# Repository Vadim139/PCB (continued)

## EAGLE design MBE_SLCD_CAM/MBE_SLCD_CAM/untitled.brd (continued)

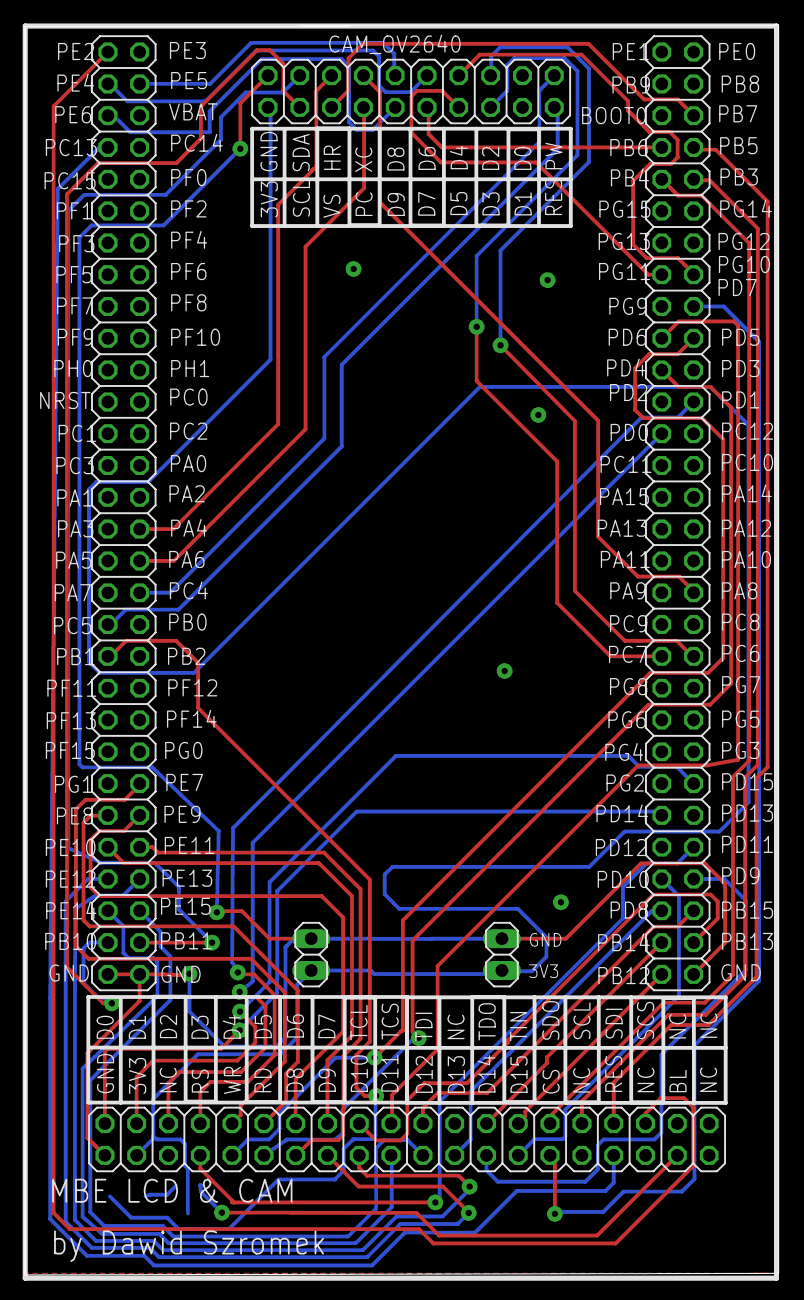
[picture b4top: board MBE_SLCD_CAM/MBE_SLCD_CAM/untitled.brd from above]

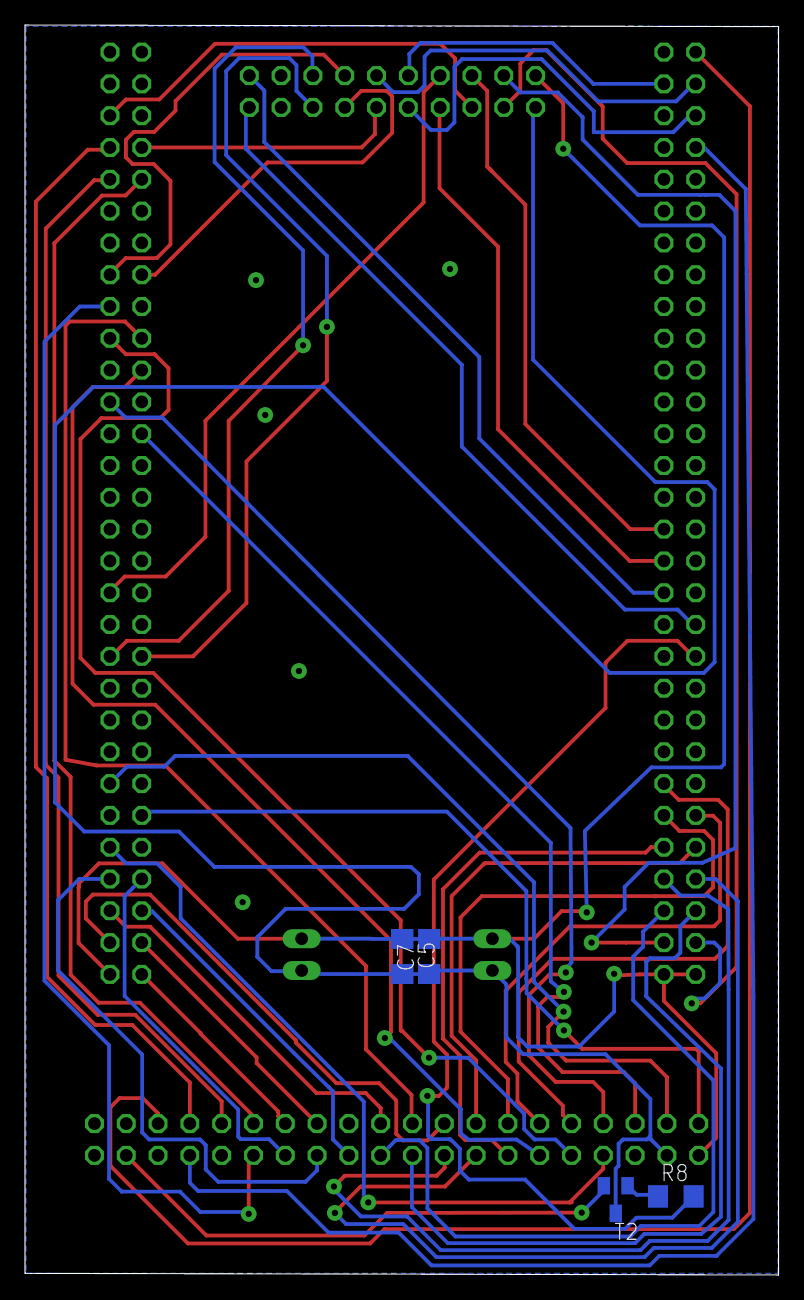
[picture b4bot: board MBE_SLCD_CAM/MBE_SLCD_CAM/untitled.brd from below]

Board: 2 copper layers, 60.2 x 99.8 mm, 7 parts (4 on the bottom side), 51 nets.

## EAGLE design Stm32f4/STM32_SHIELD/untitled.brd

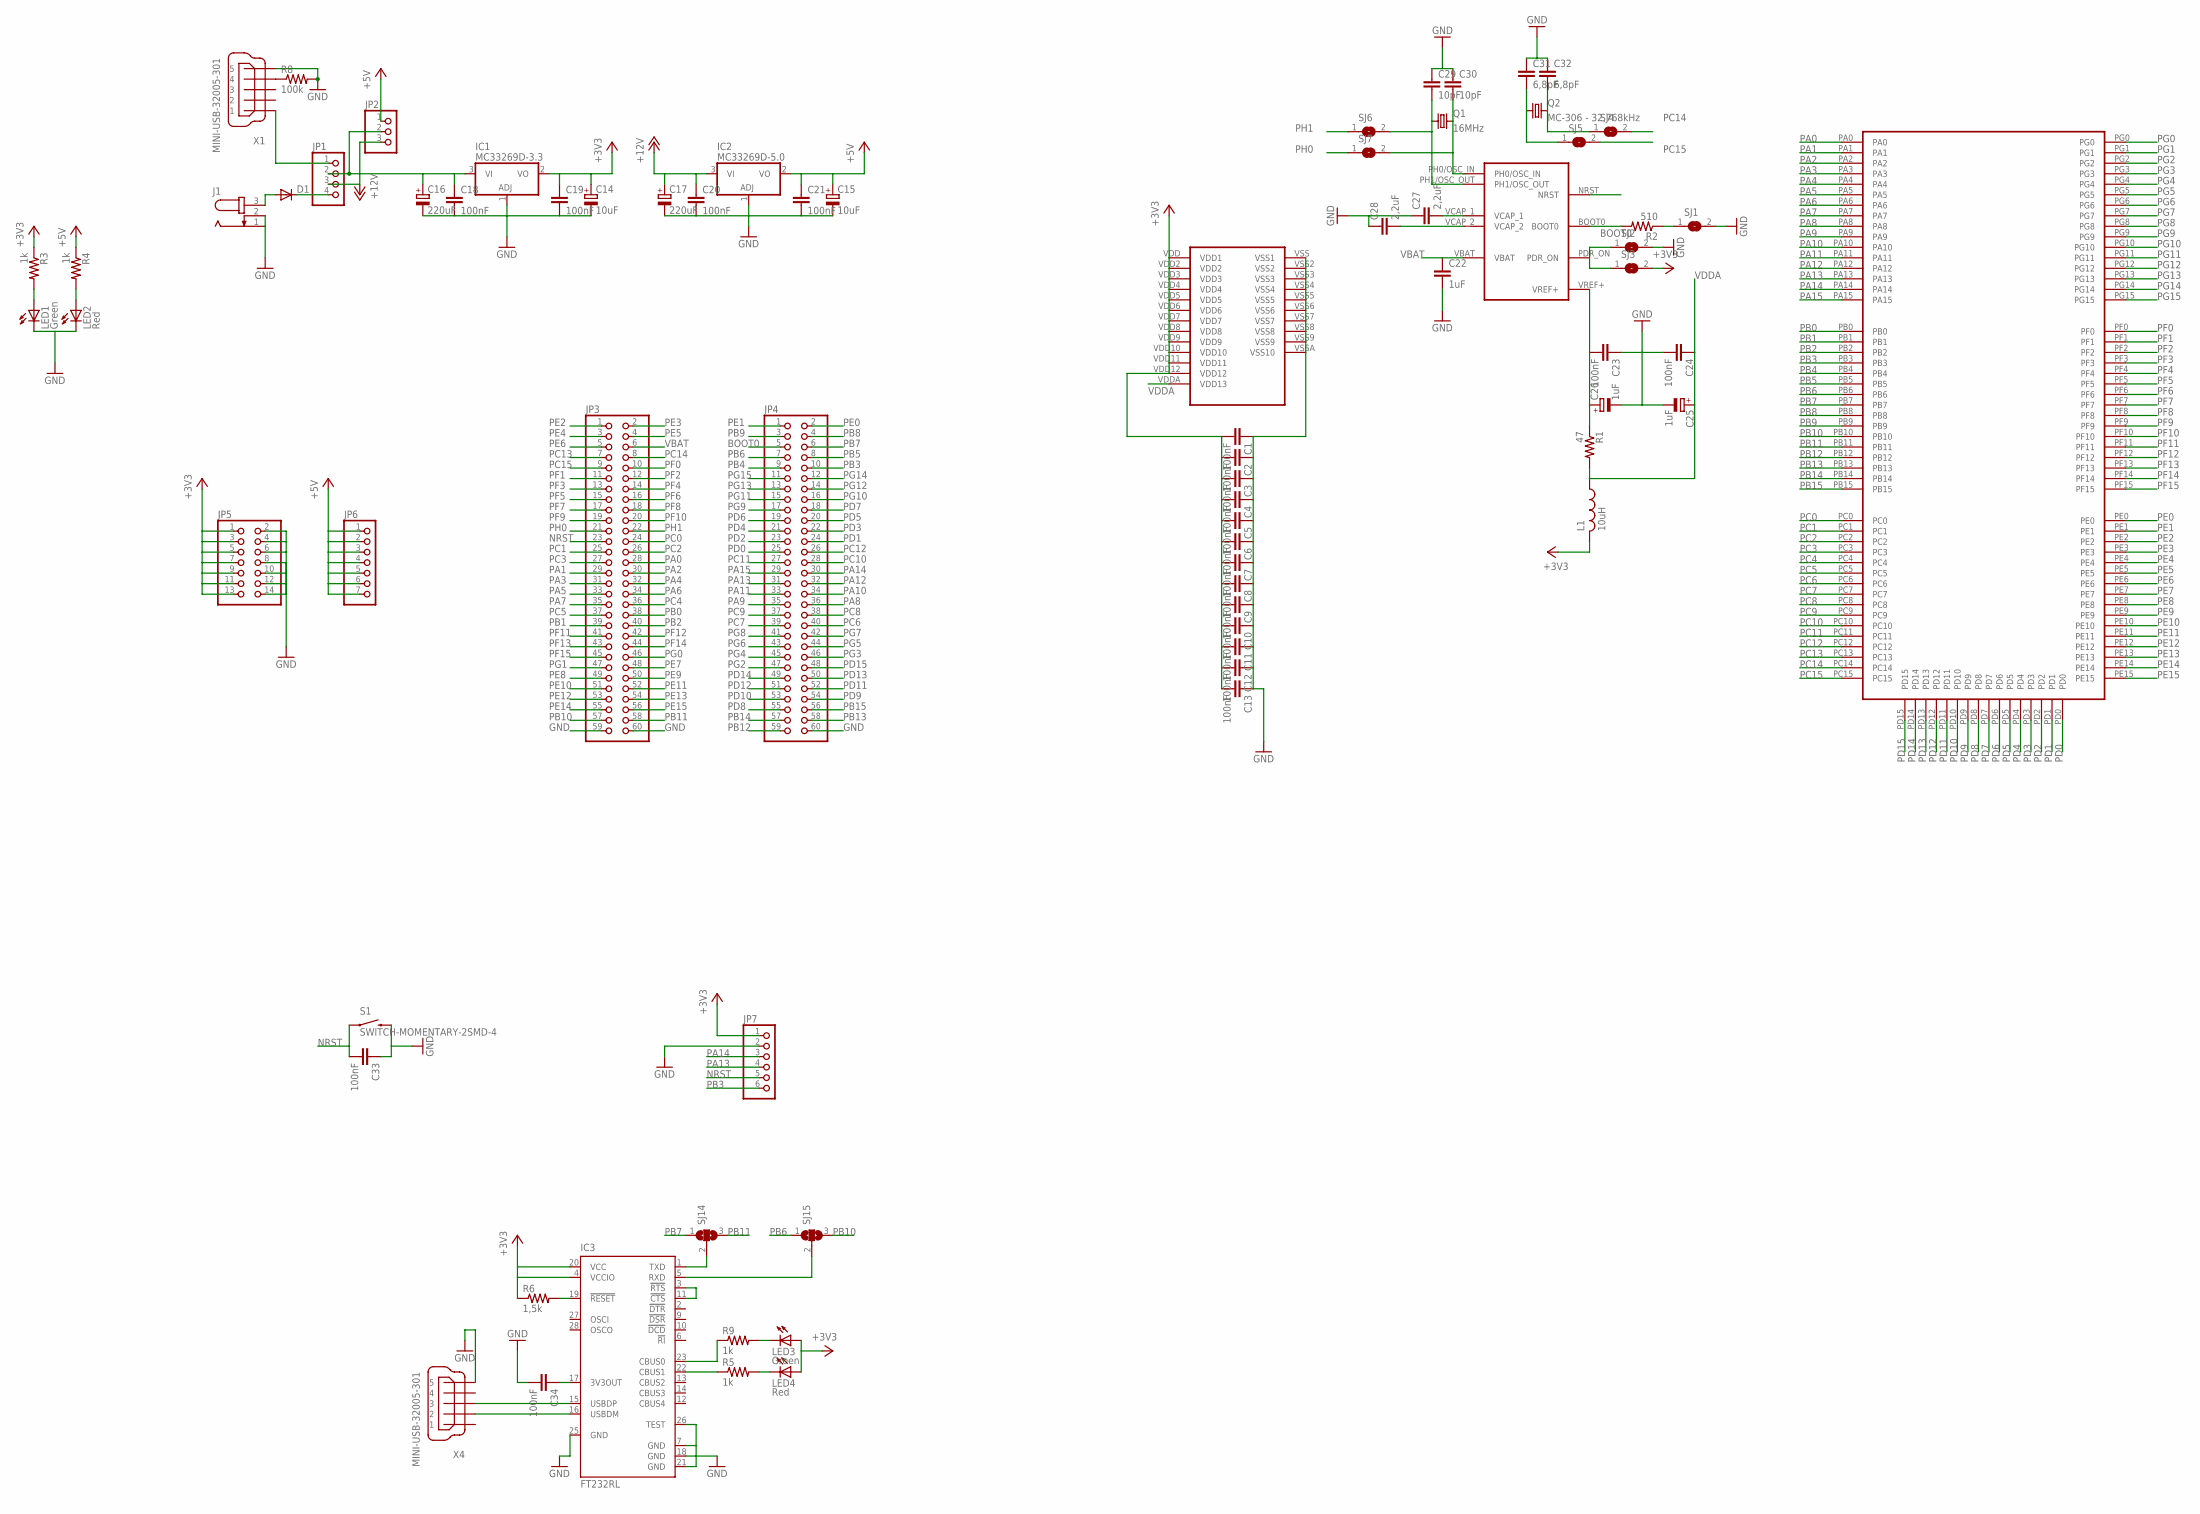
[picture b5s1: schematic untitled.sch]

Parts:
C1, C2, C3, C4, C5, C6, C7, C8, C9, C10, C11, C12, C13, C18, C19, C20, C21, C23, C24, C33, C34: 100nF; C2012
C14, C15: 10uF; SMC_C
C16, C17: 220uF; PANASONIC_D
C22: 1uF; C2012
C25, C26: 1uF; SMC_A
C27, C28: 2,2uF; C2012
C29, C30: 10pF; C2012
C31, C32: 6,8pF; C2012
D1: DIODE-SOD323-W; SOD323-W
IC1: MC33269D-3.3; DPACK
IC2: MC33269D-5.0; DPACK
IC3: FT232RL; SSOP28
J1: JACK-PLUG1; SPC4078
JP1: PINHD-1X4; 1X04
JP2: PINHD-1X3; 1X03
JP3, JP4: PINHD-2X30; 2X30
JP5: PINHD-2X7; 2X07
JP6: PINHD-1X7; 1X07
JP7: PINHD-1X6; 1X06
L1: 10uH; L2012C
LED1, LED3: Green; CHIP-LED0805
LED2, LED4: Red; CHIP-LED0805
Q1: 16MHz; HC49UP
Q2: MC-306 - 32,768kHz; MC-306
R1: 47; R0805
R2: 510; R0805
R3, R4, R5, R9: 1k; R0805
R6: 1,5k; R0805
R8: 100k; R0805
S1: SWITCH-MOMENTARY-2SMD-4; TACTILE_SWITCH_TALL
SJ1, SJ2, SJ3, SJ4, SJ5, SJ6, SJ7: SJ
SJ14, SJ15: SJ2W; SJ_2
U$1: STM32F407LQFP144; LQFP144_20
X1, X4: MINI-USB-32005-301; 32005-301

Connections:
+3V3: C1.2, C2.2, C3.2, C4.2, C5.2, C6.2, C7.2, C8.2, C9.2, C10.2, C11.2, C12.2, C13.2, C14.+, C19.1, IC1.2 (VO), IC3.4 (VCCIO), IC3.20 (VCC), JP5.1, JP5.3, JP5.5, JP5.7, JP5.9, JP5.11, JP5.13, JP7.1, L1.2, LED3.A, LED4.A, R3.1, R6.1, SJ3.2, U$1.VDD (VDD1), U$1.VDD2, U$1.VDD3, U$1.VDD4, U$1.VDD5, U$1.VDD6, U$1.VDD7, U$1.VDD8, U$1.VDD9, U$1.VDD10, U$1.VDD11, U$1.VDD12
+5V: C15.+, C21.1, IC2.2 (VO), JP2.1, JP6.1, JP6.2, JP6.3, JP6.4, JP6.5, JP6.6, JP6.7, R4.1
+12V: C17.+, C20.1, IC2.3 (VI), JP1.3, JP2.3
BOOT0: JP4.5, R2.2, U$1.BOOT0
GND: C1.1, C2.1, C3.1, C4.1, C5.1, C6.1, C7.1, C8.1, C9.1, C10.1, C11.1, C12.1, C13.1, C14.-, C15.-, C16.-, C17.-, C18.2, C19.2, C20.2, C21.2, C22.2, C23.1, C24.2, C25.-, C26.-, C27.1, C28.1, C29.1, C30.1, C31.1, C32.1, C33.1, C34.2, IC1.1 (ADJ), IC2.1 (ADJ), IC3.7 (GND), IC3.18 (GND), IC3.21 (GND), IC3.25 (GND), IC3.26 (TEST), J1.1, J1.2, JP3.59, JP3.60, JP4.60, JP5.2, JP5.4, JP5.6, JP5.8, JP5.10, JP5.12, JP5.14, JP7.2, LED1.C, LED2.C, R8.2, S1.B2 (2), SJ1.2, SJ2.2, U$1.VSS (VSS1), U$1.VSS2, U$1.VSS3, U$1.VSS4, U$1.VSS5, U$1.VSS6, U$1.VSS7, U$1.VSS8, U$1.VSS9, U$1.VSSA (VSS10), X1.5, X4.5
unnamed: JP1.1, X1.1
unnamed: D1.A, J1.3
unnamed: D1.C, JP1.4
unnamed: LED1.A, R3.2
unnamed: R2.1, SJ1.1
unnamed: LED2.A, R4.2
unnamed: C16.+, C18.1, IC1.3 (VI), JP1.2, JP2.2
unnamed: C34.1, IC3.17 (3V3OUT)
unnamed: IC3.19 (!RESET), R6.2
unnamed: IC3.23 (CBUS0), R9.1
unnamed: IC3.16 (USBDM), X4.2
unnamed: IC3.15 (USBDP), X4.3
unnamed: R8.1, X1.4
unnamed: IC3.1 (TXD), SJ14.2
unnamed: IC3.5 (RXD), SJ15.2
unnamed: SJ2.1, SJ3.1, U$1.PDR_ON
unnamed: LED3.C, R9.2
unnamed: LED4.C, R5.2
unnamed: C31.2, Q2.1, SJ5.1
unnamed: C32.2, Q2.4 (2), SJ4.1
unnamed: IC3.22 (CBUS1), R5.1
unnamed: IC3.3 (!RTS), IC3.11 (!CTS)
NRST: C33.2, JP3.23, JP7.5, S1.A2 (1), U$1.NRST
OSC_IN: C30.2, Q1.2, SJ7.2, U$1.PH0/OSC_IN
OSC_OUT: C29.2, Q1.1, SJ6.2, U$1.PH1/OSC_OUT
PA0: JP3.28, U$1.PA0
PA1: JP3.29, U$1.PA1
PA2: JP3.30, U$1.PA2
PA3: JP3.31, U$1.PA3
PA4: JP3.32, U$1.PA4
PA5: JP3.33, U$1.PA5
PA6: JP3.34, U$1.PA6
PA7: JP3.35, U$1.PA7
PA8: JP4.36, U$1.PA8
PA9: JP4.35, U$1.PA9
PA10: JP4.34, U$1.PA10
PA11: JP4.33, U$1.PA11
PA12: JP4.32, U$1.PA12
PA13: JP4.31, JP7.4, U$1.PA13
PA14: JP4.30, JP7.3, U$1.PA14
PA15: JP4.29, U$1.PA15
PB0: JP3.38, U$1.PB0
PB1: JP3.39, U$1.PB1
PB2: JP3.40, U$1.PB2
PB3: JP4.10, JP7.6, U$1.PB3
PB4: JP4.9, U$1.PB4
PB5: JP4.8, U$1.PB5
PB6: JP4.7, SJ15.1, U$1.PB6
PB7: JP4.6, SJ14.1, U$1.PB7
PB8: JP4.4, U$1.PB8
PB9: JP4.3, U$1.PB9
PB10: JP3.57, SJ15.3, U$1.PB10
PB11: JP3.58, SJ14.3, U$1.PB11
PB12: JP4.59, U$1.PB12
PB13: JP4.58, U$1.PB13
PB14: JP4.57, U$1.PB14
PB15: JP4.56, U$1.PB15
PC0: JP3.24, U$1.PC0
PC1: JP3.25, U$1.PC1
PC2: JP3.26, U$1.PC2
PC3: JP3.27, U$1.PC3
PC4: JP3.36, U$1.PC4
PC5: JP3.37, U$1.PC5
PC6: JP4.40, U$1.PC6
PC7: JP4.39, U$1.PC7
PC8: JP4.38, U$1.PC8
PC9: JP4.37, U$1.PC9
PC10: JP4.28, U$1.PC10
PC11: JP4.27, U$1.PC11
PC12: JP4.26, U$1.PC12
PC13: JP3.7, U$1.PC13
PC14: JP3.8, SJ4.2, U$1.PC14
PC15: JP3.9, SJ5.2, U$1.PC15
PD0: JP4.25, U$1.PD0
PD1: JP4.24, U$1.PD1
PD2: JP4.23, U$1.PD2
PD3: JP4.22, U$1.PD3
PD4: JP4.21, U$1.PD4
PD5: JP4.20, U$1.PD5
PD6: JP4.19, U$1.PD6
PD7: JP4.18, U$1.PD7
PD8: JP4.55, U$1.PD8
PD9: JP4.54, U$1.PD9
PD10: JP4.53, U$1.PD10
PD11: JP4.52, U$1.PD11
PD12: JP4.51, U$1.PD12
PD13: JP4.50, U$1.PD13
PD14: JP4.49, U$1.PD14
PD15: JP4.48, U$1.PD15
PE0: JP4.2, U$1.PE0
PE1: JP4.1, U$1.PE1
PE2: JP3.1, U$1.PE2
PE3: JP3.2, U$1.PE3
PE4: JP3.3, U$1.PE4
PE5: JP3.4, U$1.PE5
PE6: JP3.5, U$1.PE6
PE7: JP3.48, U$1.PE7
PE8: JP3.49, U$1.PE8
PE9: JP3.50, U$1.PE9
PE10: JP3.51, U$1.PE10
PE11: JP3.52, U$1.PE11
PE12: JP3.53, U$1.PE12
PE13: JP3.54, U$1.PE13
PE14: JP3.55, U$1.PE14
PE15: JP3.56, U$1.PE15
PF0: JP3.10, U$1.PF0
PF1: JP3.11, U$1.PF1
PF2: JP3.12, U$1.PF2
PF3: JP3.13, U$1.PF3
PF4: JP3.14, U$1.PF4
PF5: JP3.15, U$1.PF5
PF6: JP3.16, U$1.PF6
PF7: JP3.17, U$1.PF7
PF8: JP3.18, U$1.PF8
PF9: JP3.19, U$1.PF9
PF10: JP3.20, U$1.PF10
PF11: JP3.41, U$1.PF11
PF12: JP3.42, U$1.PF12
PF13: JP3.43, U$1.PF13
PF14: JP3.44, U$1.PF14
PF15: JP3.45, U$1.PF15
PG0: JP3.46, U$1.PG0
PG1: JP3.47, U$1.PG1
PG2: JP4.47, U$1.PG2
PG3: JP4.46, U$1.PG3
PG4: JP4.45, U$1.PG4
PG5: JP4.44, U$1.PG5
PG6: JP4.43, U$1.PG6
PG7: JP4.42, U$1.PG7
PG8: JP4.41, U$1.PG8
PG9: JP4.17, U$1.PG9
PG10: JP4.16, U$1.PG10
PG11: JP4.15, U$1.PG11
PG12: JP4.14, U$1.PG12
PG13: JP4.13, U$1.PG13
PG14: JP4.12, U$1.PG14
PG15: JP4.11, U$1.PG15
PH0: JP3.21, SJ7.1
PH1: JP3.22, SJ6.1
VBAT: C22.1, JP3.6, U$1.VBAT
VCAP1: C27.2, U$1.VCAP_1
VCAP2: C28.2, U$1.VCAP_2
VDDA: C24.1, C25.+, L1.1, R1.2, U$1.VDDA (VDD13)
VREF+: C23.2, C26.+, R1.1, U$1.VREF+

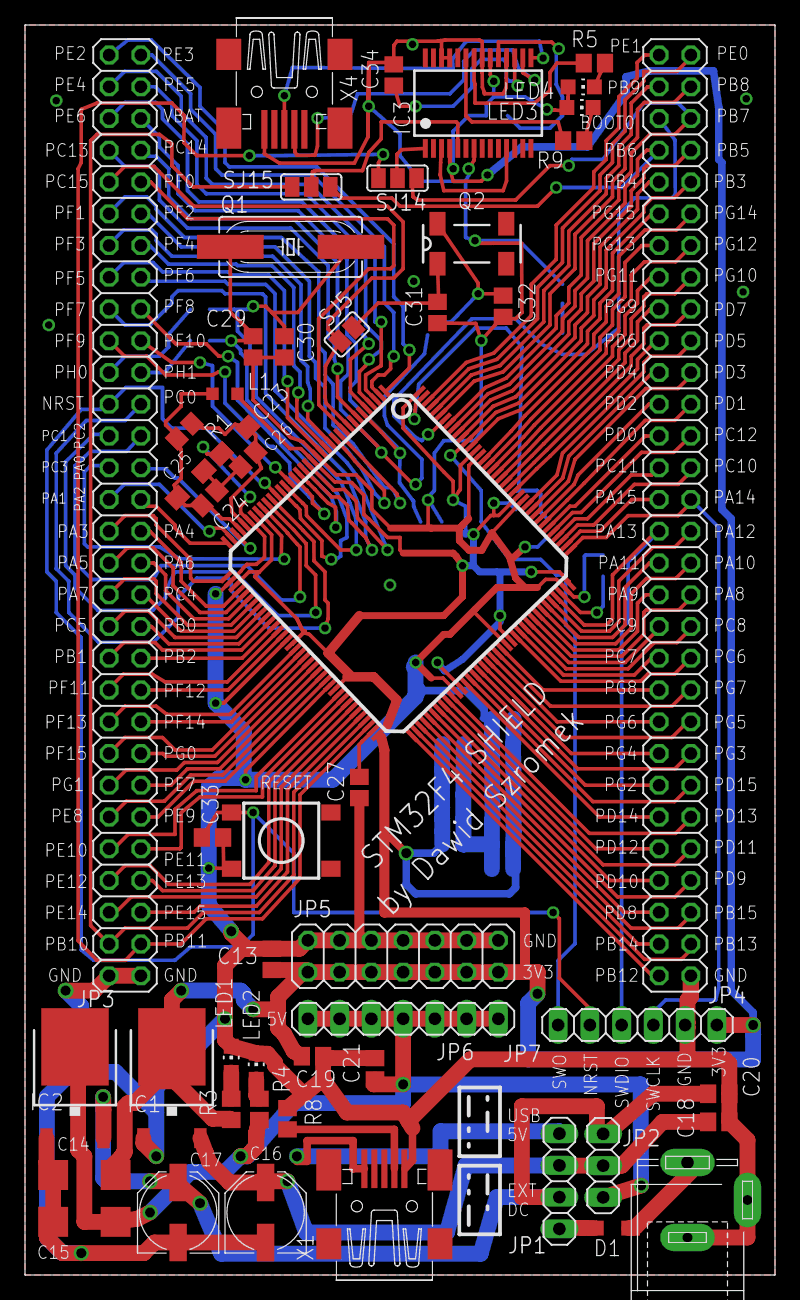
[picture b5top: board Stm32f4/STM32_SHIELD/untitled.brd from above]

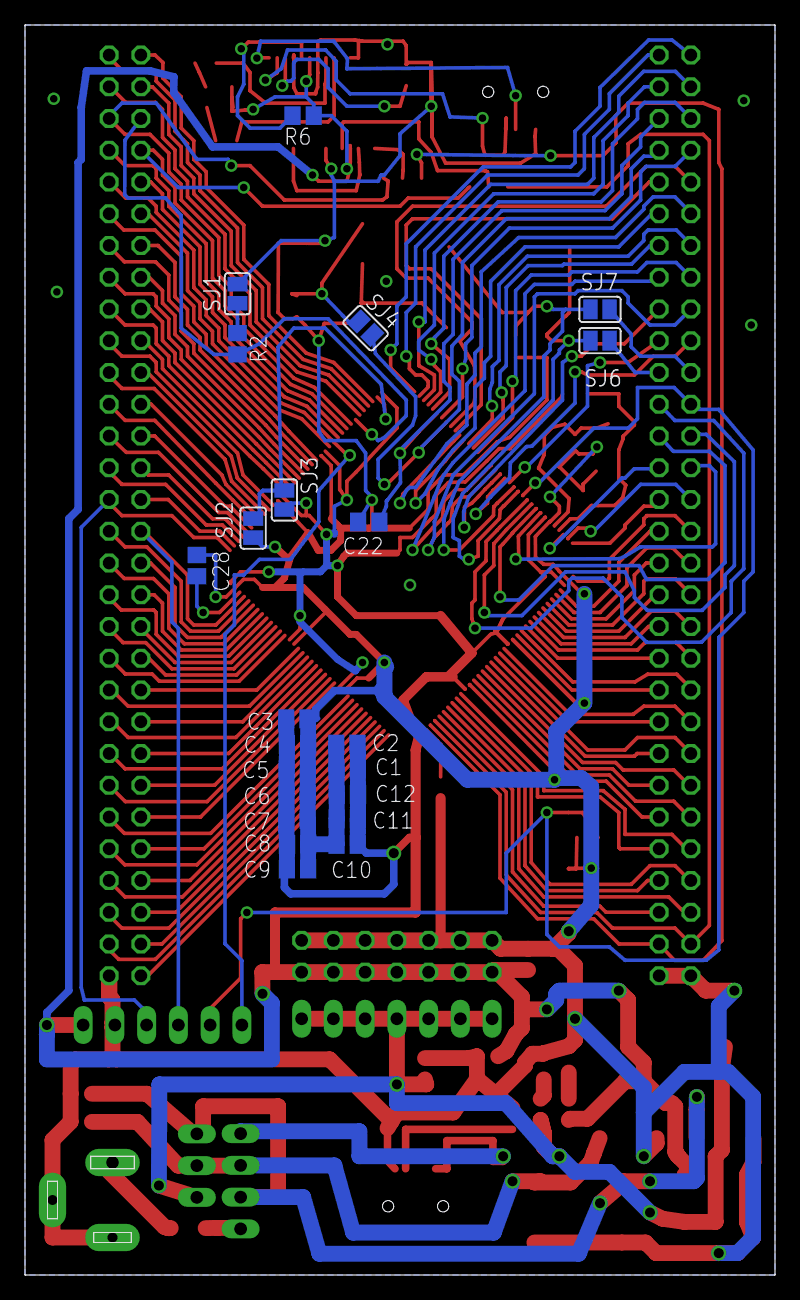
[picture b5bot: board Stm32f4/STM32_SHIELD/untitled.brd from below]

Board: 2 copper layers, 60.0 x 100.0 mm, 74 parts (22 on the bottom side), 149 nets.

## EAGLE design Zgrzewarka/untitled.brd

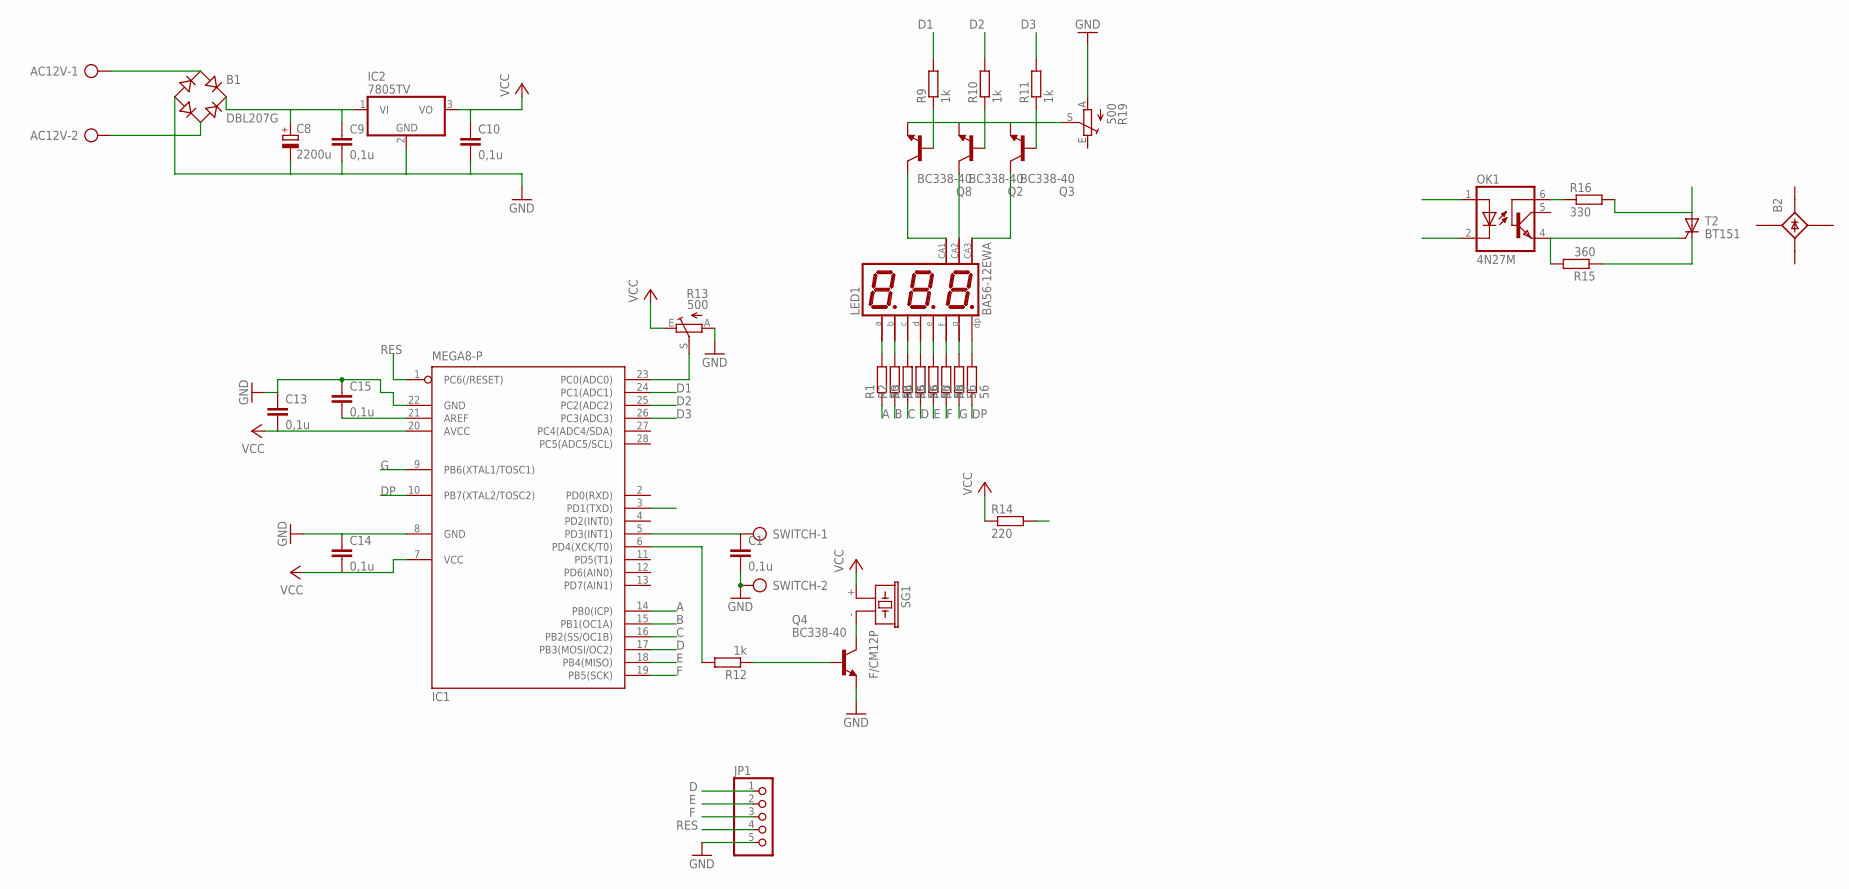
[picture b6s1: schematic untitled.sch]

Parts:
AC12V: AK500/2
B1: DBL207G; DB
B2: B25A-
C1, C9, C10, C13, C14, C15: 0,1u; C1206K
C8: 2200u; E7,5-16
IC1: MEGA8-P; DIL28-3
IC2: 7805TV; TO220V
JP1: PINHD-1X5; 1X05
LED1: BA56-12EWA; BX56-12
OK1: 4N27M; DIL06
Q2, Q3, Q4, Q8: BC338-40; TO92-EBC
R1, R2, R3, R4, R5, R6, R7, R8: 56; 0204/7
R9, R10, R11, R12: 1k; 0204/7
R13, R19: 500; CA6V
R14: 220; 0204/7
R15: 360; 0204/7
R16: 330; 0204/7
SG1: F/CM12P
SWITCH: AK500/2
T2: BT151; TO220CL

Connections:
A: IC1.14 (PB0(ICP)), R1.1
B: IC1.15 (PB1(OC1A)), R2.1
C: IC1.16 (PB2(SS/OC1B)), R3.1
C1: OK1.1 (A), R14.2
C2: IC1.3 (PD1(TXD)), OK1.2 (C)
D: IC1.17 (PB3(MOSI/OC2)), JP1.1, R4.1
D1: IC1.24 (PC1(ADC1)), R9.2
D2: IC1.25 (PC2(ADC2)), R10.2
D3: IC1.26 (PC3(ADC3)), R11.2
DP: IC1.10 (PB7(XTAL2/TOSC2)), R8.1
E: IC1.18 (PB4(MISO)), JP1.2, R5.1
F: IC1.19 (PB5(SCK)), JP1.3, R6.1
G: IC1.9 (PB6(XTAL1/TOSC1)), R7.1
GND: B1.-, C1.2, C8.-, C9.2, C10.2, C13.1, C14.1, C15.1, IC1.8 (GND), IC1.22 (GND), IC2.2 (GND), JP1.5, Q4.E, R13.A, R19.A, SWITCH.2
unnamed: LED1.11 (A), R1.2
unnamed: LED1.7 (B), R2.2
unnamed: LED1.4 (C), R3.2
unnamed: LED1.2 (D), R4.2
unnamed: LED1.1 (E), R5.2
unnamed: LED1.10 (F), R6.2
unnamed: LED1.5 (G), R7.2
unnamed: LED1.3 (DP), R8.2
unnamed: AC12V.1, B1.AC1
unnamed: AC12V.2, B1.AC2
unnamed: B1.+, C8.+, C9.1, IC2.1 (VI)
unnamed: C15.2, IC1.21 (AREF)
unnamed: LED1.12 (CA), Q8.C
unnamed: LED1.9 (CA), Q2.C
unnamed: LED1.8 (CA), Q3.C
unnamed: Q8.B, R9.1
unnamed: Q2.B, R10.1
unnamed: Q3.B, R11.1
unnamed: Q2.E, Q3.E, Q8.E, R19.S
unnamed: IC1.6 (PD4(XCK/T0)), R12.2
unnamed: Q4.B, R12.1
unnamed: Q4.C, SG1.- (2)
unnamed: C1.1, IC1.5 (PD3(INT1)), SWITCH.1
unnamed: IC1.23 (PC0(ADC0)), R13.S
unnamed: OK1.6 (BAS), R16.1
unnamed: OK1.4 (EMI), R15.2, T2.G
unnamed: R15.1, T2.C
unnamed: R16.2, T2.A
RES: IC1.1 (PC6(/RESET)), JP1.4
VCC: C10.1, C13.2, C14.2, IC1.7 (VCC), IC1.20 (AVCC), IC2.3 (VO), R13.E, R14.1, SG1.+ (1)

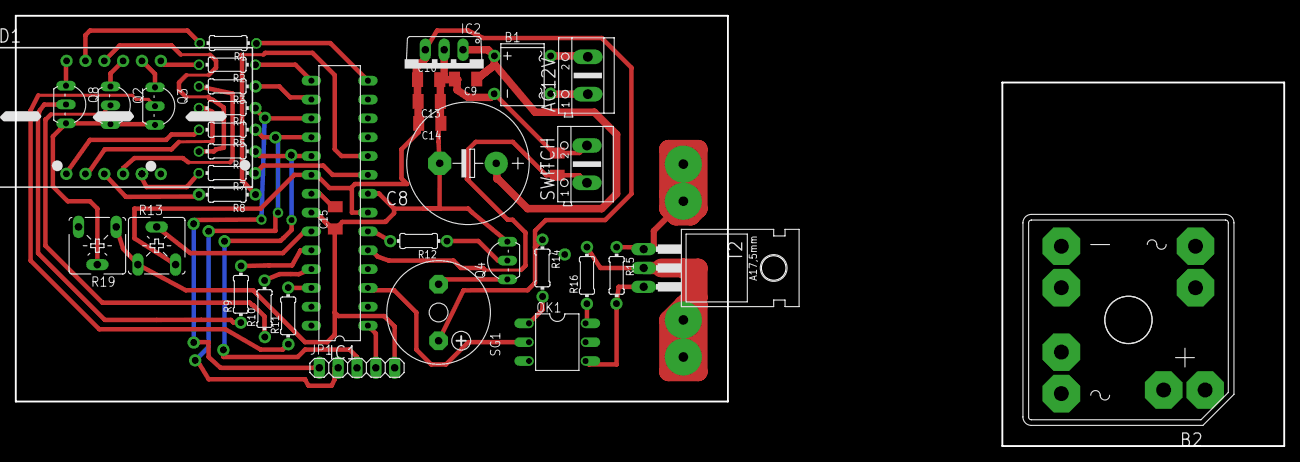
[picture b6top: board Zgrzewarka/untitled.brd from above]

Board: 2 copper layers, 96.0 x 52.0 mm, 39 parts (0 on the bottom side), 44 nets.
